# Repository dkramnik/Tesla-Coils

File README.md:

# Tesla-Coils
Tesla coil related projects and documentation.

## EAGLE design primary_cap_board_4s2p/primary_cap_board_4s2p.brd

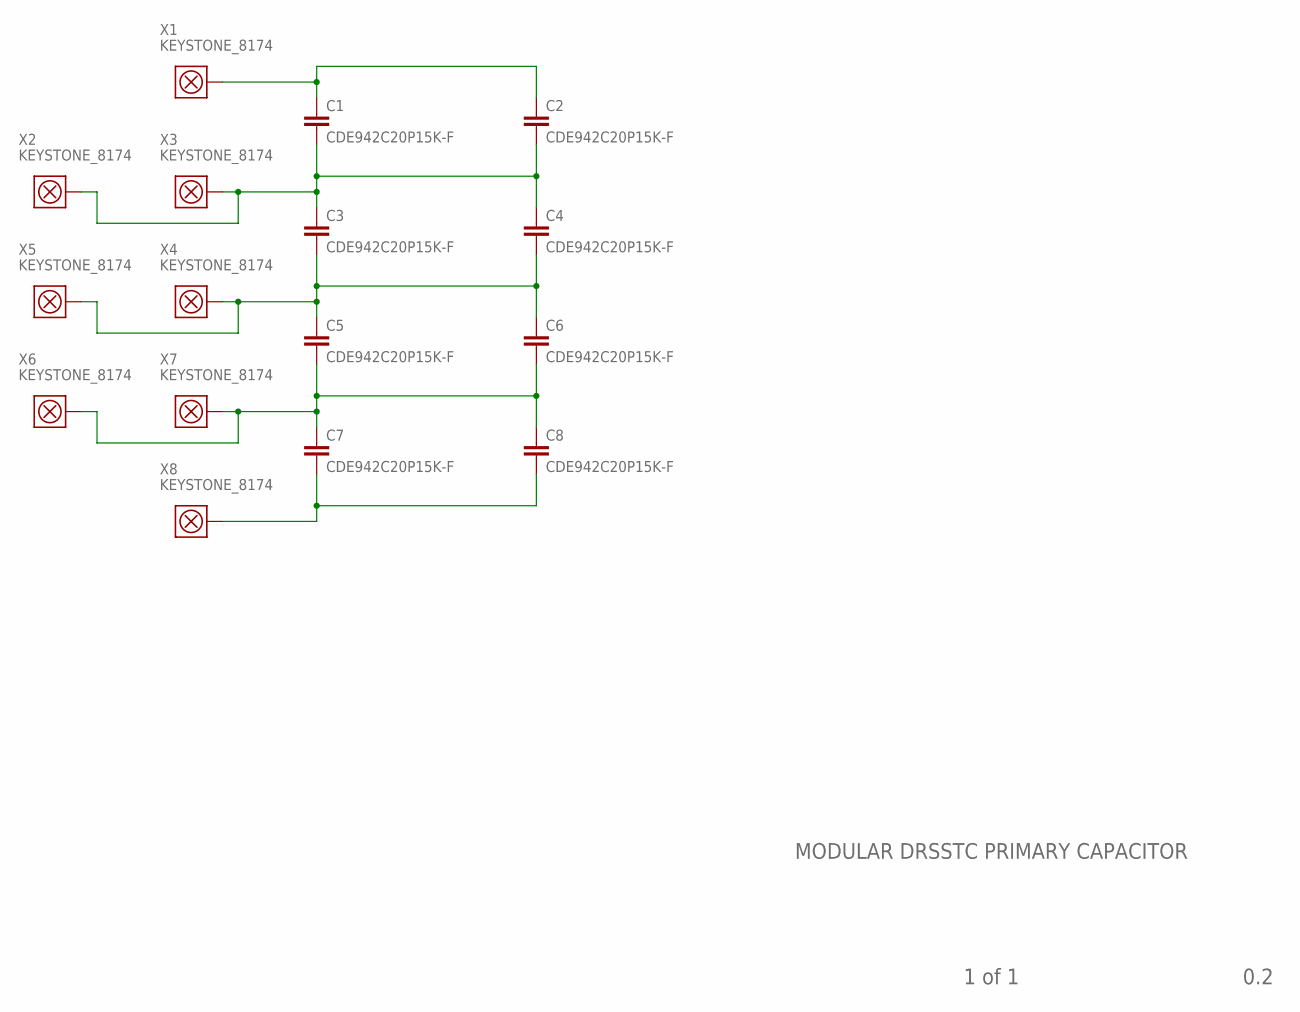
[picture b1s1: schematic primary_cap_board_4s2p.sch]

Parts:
C1, C2, C3, C4, C5, C6, C7, C8: CDE942C20P15K-F; CDE942
X1, X2, X3, X4, X5, X6, X7, X8: KEYSTONE_8174; CON_KEYSTONE_8174

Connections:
unnamed: C1.P$2 (2), C2.P$2 (2), C3.P$1 (1), C4.P$1 (1), X2.P$1, X2.P$2, X2.P$3, X2.P$4, X3.P$1, X3.P$2, X3.P$3, X3.P$4
unnamed: C3.P$2 (2), C4.P$2 (2), C5.P$1 (1), C6.P$1 (1), X4.P$1, X4.P$2, X4.P$3, X4.P$4, X5.P$1, X5.P$2, X5.P$3, X5.P$4
unnamed: C5.P$2 (2), C6.P$2 (2), C7.P$1 (1), C8.P$1 (1), X6.P$1, X6.P$2, X6.P$3, X6.P$4, X7.P$1, X7.P$2, X7.P$3, X7.P$4
unnamed: C7.P$2 (2), C8.P$2 (2), X8.P$1, X8.P$2, X8.P$3, X8.P$4
unnamed: C1.P$1 (1), C2.P$1 (1), X1.P$1, X1.P$2, X1.P$3, X1.P$4

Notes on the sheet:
0.2
1 of 1
MODULAR DRSSTC PRIMARY CAPACITOR

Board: 2 copper layers, 16 parts (0 on the bottom side), 5 nets, no tracks yet.

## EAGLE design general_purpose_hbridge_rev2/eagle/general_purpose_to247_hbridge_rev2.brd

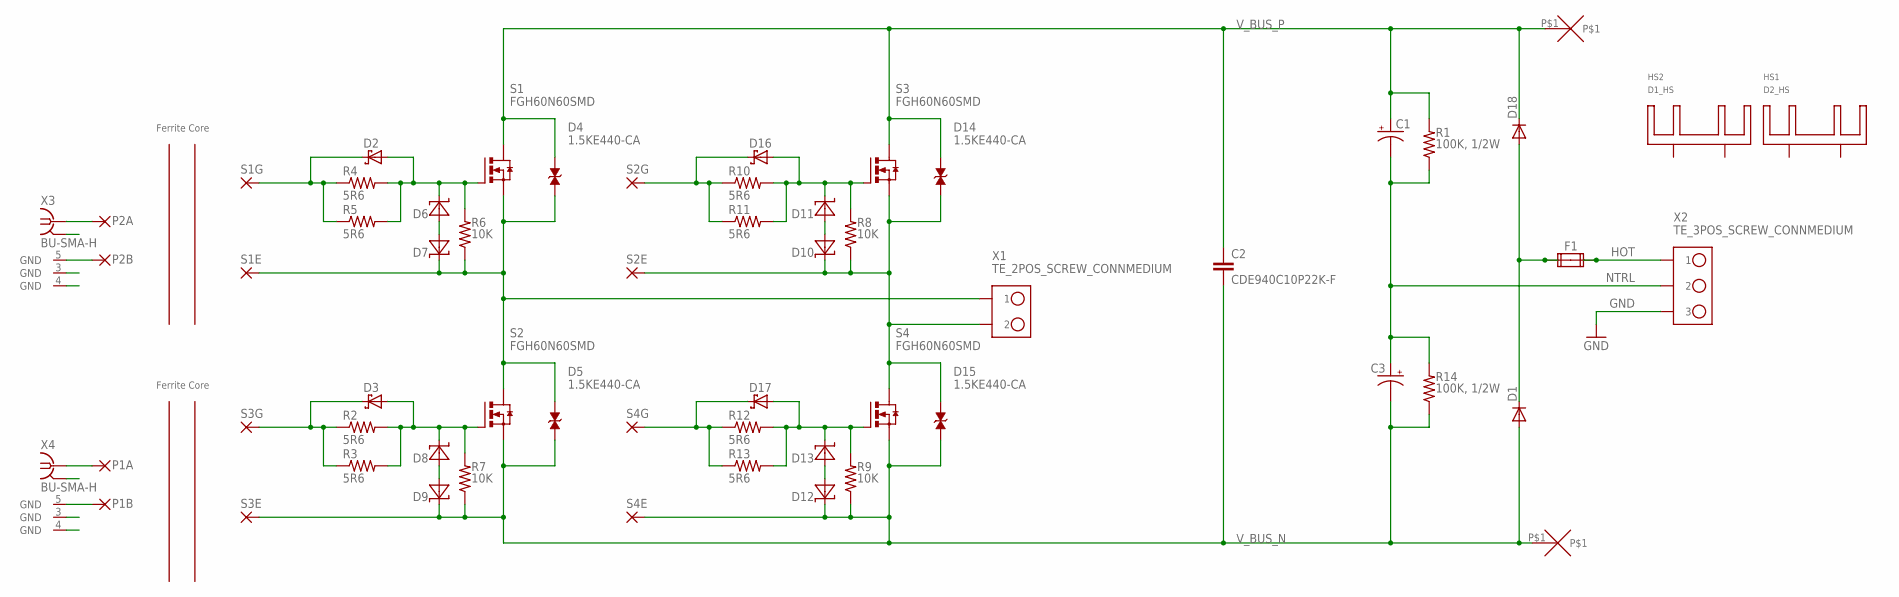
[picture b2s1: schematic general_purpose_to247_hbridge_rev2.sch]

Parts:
C1, C3: CPOL-USE10-35; EB35D
C2: CDE940C10P22K-F; 940C10P22K-F
D1, D18: DIODE-DO220S; DO220S
D2, D3, D16, D17: SCHOTTKY_SMA; SMA
D4, D5, D14, D15: 1.5KE440-CA; DO-201_BI
D6, D7, D8, D9, D10, D11, D12, D13: ZENER_SMA; SMA
F1: FUSE2P; FUSE1
HS1: D2_HS; V6560_HEATSINK_REVERSED
HS2: D1_HS; V6560_HEATSINK_REVERSED
P1A, P1B, P2A, P2B: SMD5; SMD2,54-5,08
R1, R14: 100K, 1/2W; 0309/12
R2, R4, R10, R12: 5R6; R2010
R3, R5, R11, R13: 5R6; R0805
R6, R7, R8, R9: 10K; R0805
S1, S2, S3, S4: FGH60N60SMD; TO247_H_NOHOLE
S1E, S1G, S2E, S2G, S3E, S3G, S4E, S4G: SMD5; SMD2,54-5,08
U$1, U$3: 12AWG_PAD
U$2, U$4: GDT_SYMBOL; GDT
X1: TE_2POS_SCREW_CONNMEDIUM; OST_2POS_SCREW_CON_OSTYK51102030
X2: TE_3POS_SCREW_CONNMEDIUM; OST_2POS_SCREW_CON_SOTYK51103030
X3, X4: BU-SMA-H

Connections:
GND: X2.P$3 (3)
HOT: F1.2A, F1.2B, X2.P$1 (1)
unnamed: P1B.1, X4.5 (GND)
unnamed: D1.C, D18.A, F1.1A, F1.1B
unnamed: D11.C, D16.A, R8.2, R10.2, R11.2, S3.G
unnamed: P2B.1, X3.5 (GND)
unnamed: D13.C, D17.A, R9.2, R12.2, R13.2, S4.G
unnamed: D3.A, D8.C, R2.2, R3.2, R7.2, S2.G
unnamed: D6.A, D7.A
unnamed: D2.A, D6.C, R4.2, R5.2, R6.2, S1.G
unnamed: D8.A, D9.A
unnamed: D12.A, D13.A
unnamed: D10.A, D11.A
unnamed: P1A.1, X4.1
unnamed: P2A.1, X3.1
NTRL: C1.-, C3.+, R1.1, R14.2, X2.P$2 (2)
S1E: D4.A, D5.C, D7.C, R6.1, S1.S, S1E.1, S2.D, X1.P$1 (1)
S1G: D2.C, R4.1, R5.1, S1G.1
S2E: D10.C, D14.A, D15.C, R8.1, S2E.1, S3.S, S4.D, X1.P$2 (2)
S2G: D16.C, R10.1, R11.1, S2G.1
S3G: D3.C, R2.1, R3.1, S3G.1
S4G: D17.C, R12.1, R13.1, S4G.1
V_BUS_N: C2.P$2 (2), C3.-, D1.A, D5.A, D9.C, D12.C, D15.A, R7.1, R9.1, R14.1, S2.S, S3E.1, S4.S, S4E.1, U$1.P$1
V_BUS_P: C1.+, C2.P$1 (1), D4.C, D14.C, D18.C, R1.2, S1.D, S3.D, U$3.P$1

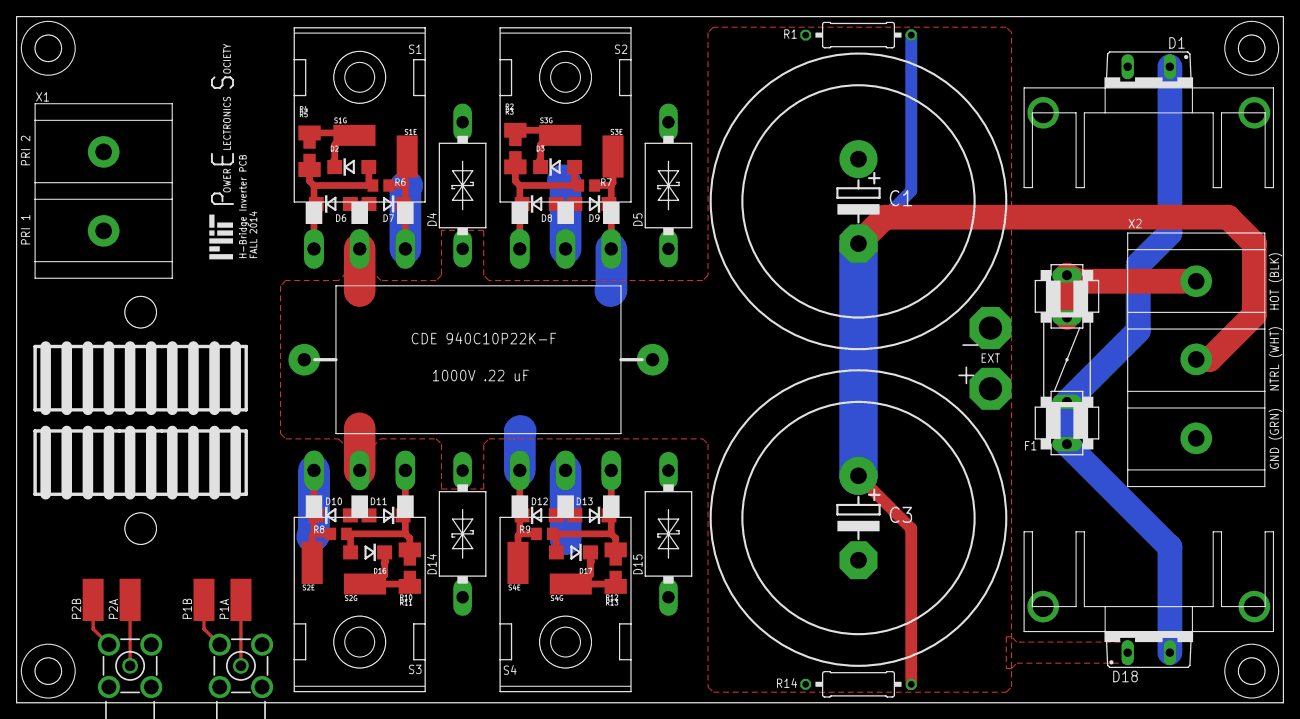
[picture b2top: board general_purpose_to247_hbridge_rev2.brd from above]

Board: 2 copper layers, 152.4 x 82.5 mm, 62 parts (0 on the bottom side), 23 nets.

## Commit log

2016-07-04 General purpose bridge (rev2) design files added.
2020-01-15 Added MDX box schematics
2021-06-21 Copy over primary cap board from modular DRSSTC folder
